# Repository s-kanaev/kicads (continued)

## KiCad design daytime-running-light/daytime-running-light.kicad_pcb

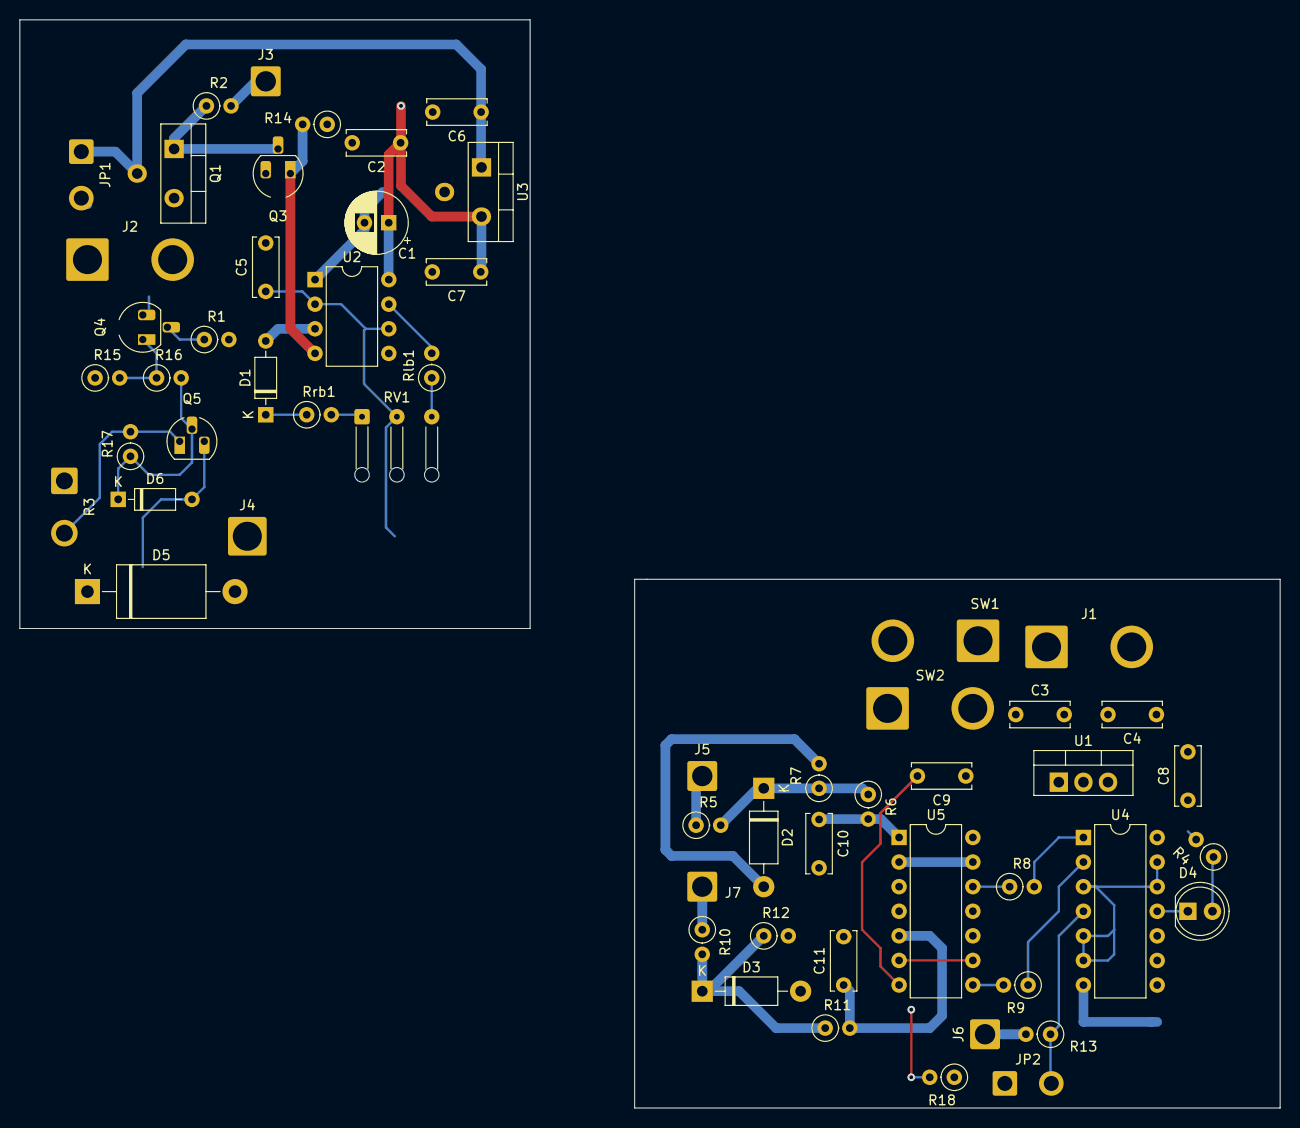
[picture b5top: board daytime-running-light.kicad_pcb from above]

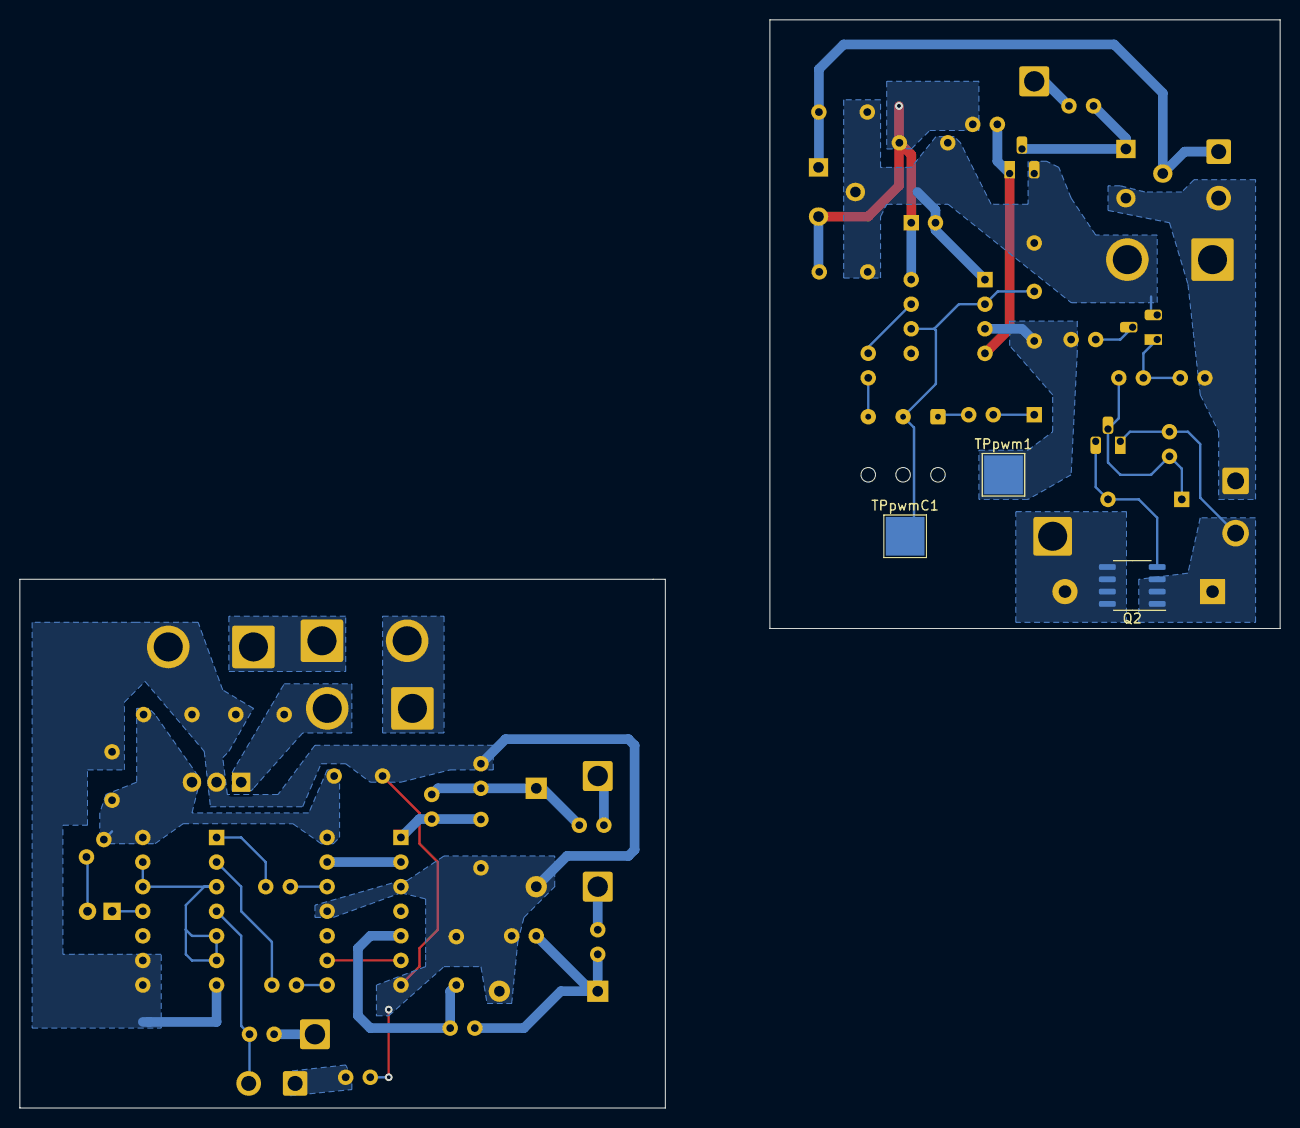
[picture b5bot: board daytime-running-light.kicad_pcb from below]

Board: 2 copper layers, 130.2 x 112.4 mm, 61 parts (3 on the bottom side), 42 nets.

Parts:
C1: 0.1u; CP_Radial_D6.3mm_P2.50mm
C2: 0.1u; C_Disc_D6.0mm_W2.5mm_P5.00mm
C3, C6, C10, C11: 0.33uF; C_Disc_D6.0mm_W2.5mm_P5.00mm
C4, C7, C8, C9: 0.1uF; C_Disc_D6.0mm_W2.5mm_P5.00mm
C5: 33n; C_Disc_D6.0mm_W2.5mm_P5.00mm
D1: BAT42; D_DO-35_SOD27_P7.62mm_Horizontal
D2: 1N47xxA; D_DO-41_SOD81_P10.16mm_Horizontal
D3: 1N4742A; D_DO-41_SOD81_P10.16mm_Horizontal
D4: LED; LED_D5.0mm
D5: 1.5KExxA; D_DO-201AE_P15.24mm_Horizontal
D6: 1N4148; D_DO-35_SOD27_P7.62mm_Horizontal
J1, J2: Conn_01x02_Socket; SolderWire-2.5sqmm_1x02_P8.8mm_D2.4mm_OD4.4mm
J3, J5, J7: Conn_01x01_Socket; SolderWire-1.5sqmm_1x01_D1.7mm_OD3mm
J4: Conn_01x01_Socket; SolderWire-2.5sqmm_1x01_D2.4mm_OD3.6mm
J6: Conn_01x01_Pin; SolderWire-1.5sqmm_1x01_D1.7mm_OD3mm
JP1, JP2: Jumper_2_Open; SolderWire-0.75sqmm_1x02_P4.8mm_D1.25mm_OD2.3mm
Q1: IRF9540N; TO-220-3_Vertical-mod
Q2: IRF9321; SO-8_3.9x4.9mm_P1.27mm
Q3, Q4: BC548; TO-92_HandSolder2
Q5: BC548; TO-92_HandSolder
R1, R2, R17: 10k; R_Axial_DIN0207_L6.3mm_D2.5mm_P2.54mm_Vertical
R3: 0.2; SolderWire-1sqmm_1x02_P5.4mm_D1.4mm_OD2.7mm
R4, R18: R; R_Axial_DIN0207_L6.3mm_D2.5mm_P2.54mm_Vertical
R5, R8, R9, R10: 1k; R_Axial_DIN0207_L6.3mm_D2.5mm_P2.54mm_Vertical
R6, R11: 47k; R_Axial_DIN0207_L6.3mm_D2.5mm_P2.54mm_Vertical
R7, R12: 100k; R_Axial_DIN0207_L6.3mm_D2.5mm_P2.54mm_Vertical
R13, R16: 100; R_Axial_DIN0207_L6.3mm_D2.5mm_P2.54mm_Vertical
R14, R15: 10k..100k; R_Axial_DIN0207_L6.3mm_D2.5mm_P2.54mm_Vertical
RV1: 51k; SolderWire-0.1sqmm_1x03_P3.6mm_D0.4mm_OD1mm_Relief
Rlb1: 51k; R_Axial_DIN0207_L6.3mm_D2.5mm_P2.54mm_Vertical
Rrb1: 1k; R_Axial_DIN0207_L6.3mm_D2.5mm_P2.54mm_Vertical
SW1, SW2: SW_SPST; SolderWire-2.5sqmm_1x02_P8.8mm_D2.4mm_OD4.4mm
TPpwm1: TestPoint; TestPoint_Pad_4.0x4.0mm
TPpwmC1: TestPoint; TestPoint_Pad_4.0x4.0mm
U1: L7812; TO-220-3_Vertical
U2: TLC555xP; DIP-8_W7.62mm
U3: L7812; TO-220-3_Vertical-mod
U4: 4001; DIP-14_W7.62mm
U5: 4069; DIP-14_W7.62mm

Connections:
+12V: J2.1, JP1.2 (B), Q1.3 (S), R3.1, R15.1
/ALLOW_POWER_ON: Q1.1 (G), Q3.2 (B), R2.1
/HEADLIGHT: J5.1, R5.1
/HIGHBEAM: J7.1, R10.1
/POWER_CONTROL: D1.2 (A), R1.2, TPpwm1.1, U2.3 (Q)
/POWER_CONTROL_INV: Q4.1 (C), R15.2, R16.1
/U1_DISCH: Rlb1.2, U2.7 (DIS)
/U1_TR: C5.1, RV1.2, TPpwmC1.1, U2.2 (TR), U2.6 (THR)
/VCC_STAB: C4.1, C8.1, C9.1, R4.2, U1.3 (OUT), U4.14 (VDD), U5.14 (VDD)
/VCC_STAB2: C1.1, C2.1, C7.1, R14.1, U2.8 (VCC), U3.3 (OUT)
GND: C3.2, C4.2, C8.2, C9.2, C10.2, C11.2, D2.2 (A), D3.2 (A), J1.2, R7.2, R12.2, R18.2, U1.2 (GND), U4.7 (VSS), U4.8, U4.9, U5.3, U5.7 (VSS), U5.11
GND2: C1.2, C2.2, C5.2, C6.2, C7.2, J2.2, Q3.3 (E), Q4.3 (E), U2.1 (GND), U3.2 (GND)
unnamed: C10.1, R6.2, U5.1
unnamed: C11.1, R11.2, U5.5
unnamed: D1.1 (K), Rrb1.1
unnamed: D2.1 (K), R5.2, R6.1, R7.1
unnamed: D3.1 (K), R10.2, R11.1, R12.1
unnamed: D4.2 (A), R4.1
unnamed: D4.1 (K), U4.11
unnamed: D5.1 (A1), Q2.3 (S), Q5.1 (C), R3.2, R17.2
unnamed: D5.2 (A2), J4.1, Q2.1 (D)
unnamed: D6.2 (A), Q2.2 (G), Q5.3 (E)
unnamed: D6.1 (K), Q5.2 (B), R16.2, R17.1
unnamed: J3.1, R2.2
unnamed: J6.1, R13.2
unnamed: C6.1, JP1.1 (A), Q1.2 (D), U3.1 (IN)
unnamed: JP2.1 (A), R18.1
unnamed: JP2.2 (B), R13.1, U4.4
unnamed: Q3.1 (C), R14.2, U2.4 (R)
unnamed: Q4.2 (B), R1.1
unnamed: R8.1, U5.12
unnamed: R8.2, U4.1
unnamed: R9.1, U4.2
unnamed: R9.2, U5.8
unnamed: RV1.1, Rrb1.2
unnamed: RV1.3, Rlb1.1
unnamed: SW1.2 (B), SW2.1 (A)
unnamed: C3.1, SW2.2 (B), U1.1 (IN)
unnamed: U4.3, U4.5, U4.6, U4.12, U4.13
unnamed: U5.6, U5.9
unnamed: U5.2, U5.13
VCC: J1.1, SW1.1 (A)

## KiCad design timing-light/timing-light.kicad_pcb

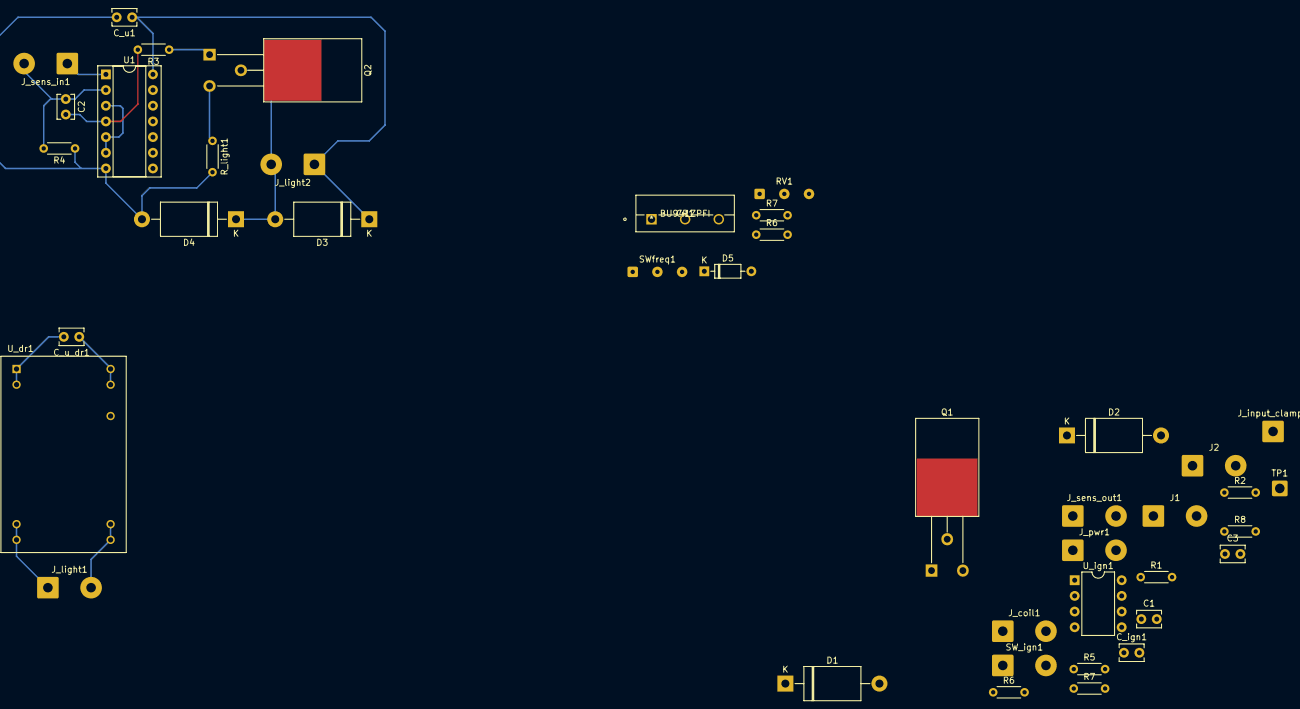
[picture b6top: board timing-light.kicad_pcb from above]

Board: 2 copper layers, 41 parts (0 on the bottom side), 28 nets.

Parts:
C1: 68pF; C_Disc_D3.8mm_W2.6mm_P2.50mm
C2: 0.1uF; C_Disc_D3.8mm_W2.6mm_P2.50mm
C3: 6.8uF; C_Disc_D3.8mm_W2.6mm_P2.50mm
CR1: BU941ZPFI
C_ign1: 0.1uF; C_Disc_D3.8mm_W2.6mm_P2.50mm
C_u1: 0.1uF; C_Disc_D3.8mm_W2.6mm_P2.50mm
C_u_dr1: 0.1uF; C_Disc_D3.8mm_W2.6mm_P2.50mm
D1, D2, D3, D4: 1.5KExxA; D_DO-201AE_P15.24mm_Horizontal
D5: BAT42; D_DO-35_SOD27_P7.62mm_Horizontal
J1: Conn_01x02_Male; SolderWire-0.75sqmm_1x02_P7mm_D1.25mm_OD3.5mm
J2: Conn_01x02_Female; SolderWire-0.75sqmm_1x02_P7mm_D1.25mm_OD3.5mm
J_coil1: Conn_01x02_Male; SolderWire-0.75sqmm_1x02_P7mm_D1.25mm_OD3.5mm
J_input_clamp1: Conn_01x01_Female; SolderWire-0.75sqmm_1x01_D1.25mm_OD3.5mm
J_light1, J_light2: Conn_01x02_Male; SolderWire-0.75sqmm_1x02_P7mm_D1.25mm_OD3.5mm
J_pwr1: Conn_01x02_Female; SolderWire-0.75sqmm_1x02_P7mm_D1.25mm_OD3.5mm
J_sens_in1: Conn_01x02_Female; SolderWire-0.75sqmm_1x02_P7mm_D1.25mm_OD3.5mm
J_sens_out1: Conn_01x02_Male; SolderWire-0.75sqmm_1x02_P7mm_D1.25mm_OD3.5mm
Q1, Q2: IRFB3004PbF; TO-220-3-4_Horizontal_TabDown
R1, R6, R7: 15k; R_Axial_DIN0204_L3.6mm_D1.6mm_P5.08mm_Horizontal
R2: 3k; R_Axial_DIN0204_L3.6mm_D1.6mm_P5.08mm_Horizontal
R3: 1k/4.7k; R_Axial_DIN0204_L3.6mm_D1.6mm_P5.08mm_Horizontal
R4: 100k; R_Axial_DIN0204_L3.6mm_D1.6mm_P5.08mm_Horizontal
R5: R; R_Axial_DIN0204_L3.6mm_D1.6mm_P5.08mm_Horizontal
R6#2, R7#2: 1k; R_Axial_DIN0204_L3.6mm_D1.6mm_P5.08mm_Horizontal
R8: 68k; R_Axial_DIN0204_L3.6mm_D1.6mm_P5.08mm_Horizontal
RV1: 470k; SolderWire-0.15sqmm_1x03_P4mm_D0.5mm_OD1.5mm
R_light1: R; R_Axial_DIN0204_L3.6mm_D1.6mm_P5.08mm_Horizontal
SW_ign1: SW_SPST; SolderWire-0.75sqmm_1x02_P7mm_D1.25mm_OD3.5mm
SWfreq1: SW_SPDT; SolderWire-0.15sqmm_1x03_P4mm_D0.5mm_OD1.5mm
TP1: TestPoint; SolderWire-0.75sqmm_1x01_D1.25mm_OD2.3mm
U1: 4001; DIP-14_W7.62mm_Socket
U_dr1: LDB600; MEANWELL_LDB-350L
U_ign1: TLC555xP; DIP-8_W7.62mm

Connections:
+12V: C_u1.1, C_u_dr1.1, D1.1 (A1), D3.1 (A1), J_coil1.1, J_light2.1, J_pwr1.2, SW_ign1.1 (A), U1.14 (VDD), U_dr1.23 (+Vin), U_dr1.24 (+Vin)
/U_ign_pwr: C_ign1.1, SW_ign1.2 (B), U_ign1.4 (R), U_ign1.8 (VCC)
/U_ign_tr: C3.1, R7.2, R8.2
/Uign_dis: R7#2.2, U_ign1.7 (DIS)
/Uign_trig: RV1.2, SWfreq1.2 (B), U_ign1.2 (TR), U_ign1.6 (THR)
/on_off_dr: Q2.1 (G), R3.1, U_dr1.21 (PWM_DIM)
GND: C3.2, CR1.3 (E), C_ign1.2, C_u1.2, C_u_dr1.2, D2.2 (A2), D4.2 (A2), J1.1, J2.1, J_pwr1.1, Q1.3, R4.1, R_light1.2, U1.7 (VSS), U_dr1.1 (-Vin), U_dr1.2 (-Vin), U_ign1.1 (GND)
unnamed: C1.1, R1.2, R2.2
unnamed: C1.2, J_input_clamp1.1
unnamed: C2.1, J_sens_in1.2, R4.2, U1.2
unnamed: C2.2, R3.2, U1.4
unnamed: CR1.1 (B), J2.2
unnamed: CR1.2 (C), D1.2 (A2), D2.1 (A1), J_coil1.2
unnamed: Q1.2, Q1.4
unnamed: D3.2 (A2), D4.1 (A1), J_light2.2, Q2.2 (D), Q2.4 (D)
unnamed: D5.1 (K), R6#2.1
unnamed: D5.2 (A), R5.2, TP1.1, U_ign1.3 (Q)
unnamed: J1.2, R5.1
unnamed: J_light1.1, U_dr1.11 (-Vout), U_dr1.12 (-Vout)
unnamed: J_light1.2, U_dr1.13 (+Vout), U_dr1.14 (+Vout)
unnamed: J_sens_in1.1, U1.1
unnamed: J_sens_out1.1, R1.1
unnamed: J_sens_out1.2, R2.1
unnamed: Q2.3 (S), R_light1.1
unnamed: R6.1, R7.1
unnamed: R6.2, R6#2.2, R8.1, RV1.3
unnamed: R7#2.1, RV1.1
unnamed: U1.3, U1.5, U1.6

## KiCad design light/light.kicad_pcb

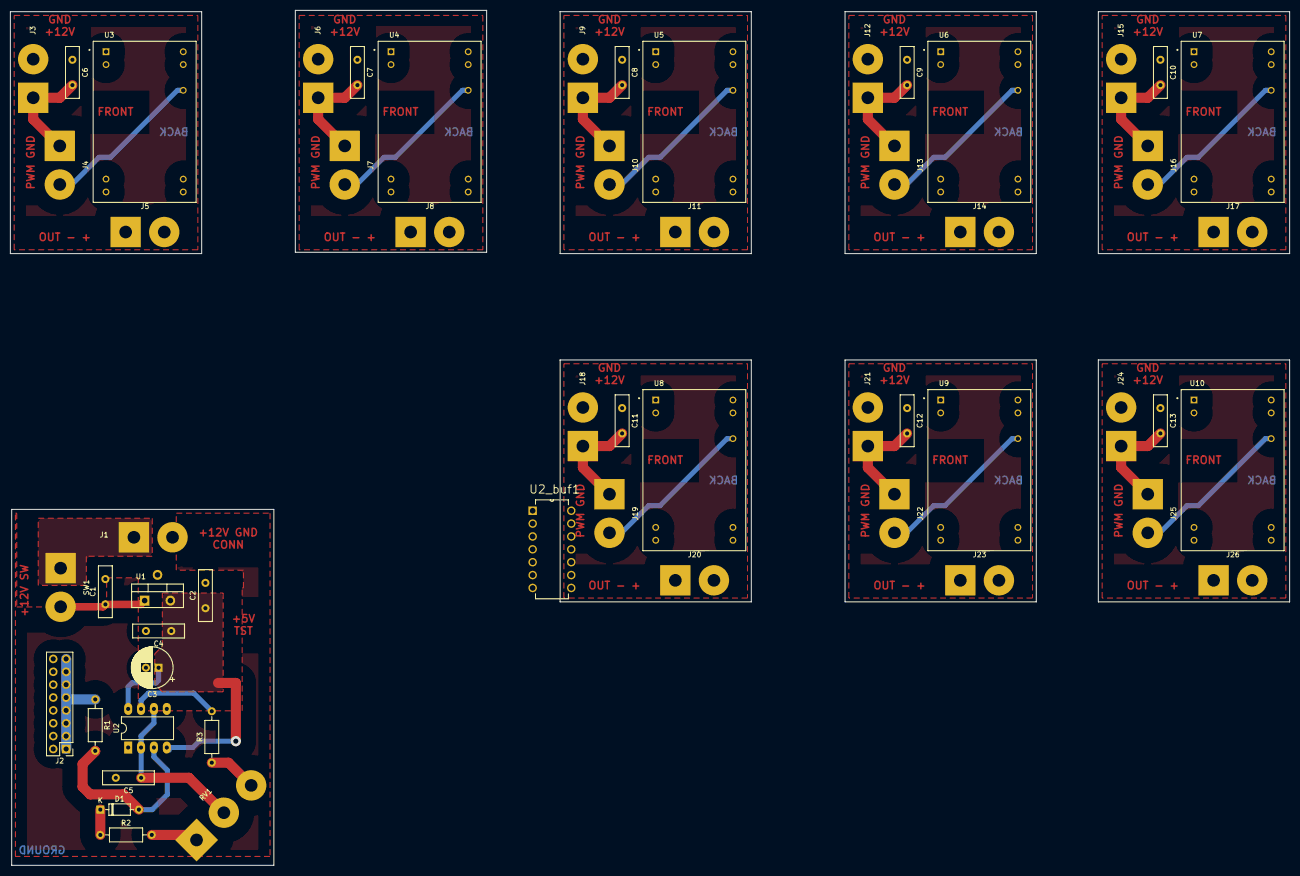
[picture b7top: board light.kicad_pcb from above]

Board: 2 copper layers, 252.5 x 168.8 mm, 56 parts (0 on the bottom side), 55 nets.

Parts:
C1: 0.33u; C_Disc_D10.0mm_W2.5mm_P5.00mm
C2, C4: 0.1u; C_Disc_D10.0mm_W2.5mm_P5.00mm
C3: 1u; CP_Radial_D8.0mm_P2.50mm
C5: 33n; C_Disc_D10.0mm_W2.5mm_P5.00mm
C6, C7, C8, C9, C10, C11, C12, C13: 1u; C_Disc_D10.0mm_W2.5mm_P5.00mm
D1: BAT42; D_DO-35_SOD27_P7.62mm_Horizontal
J1, J3, J4, J6, J7, J9, J10, J12, J13, J15, J16, J18, J19, J21, J22, J24, J25: Conn_01x02_Female; SolderWirePad_1x02_P7.62mm_Drill2.5mm
J2: Conn_02x08_Odd_Even; PinHeader_2x08_P2.54mm_Vertical
J5, J8, J11, J14, J17, J20, J23, J26: Conn_01x02_Male; SolderWirePad_1x02_P7.62mm_Drill2.5mm
R1: 100; R_Axial_DIN0207_L6.3mm_D2.5mm_P10.16mm_Horizontal
R2, R3: 1k; R_Axial_DIN0207_L6.3mm_D2.5mm_P10.16mm_Horizontal
RV1: 100k; SolderWirePad_1x03_P7.62mm_Drill2.5mm
SW1: SW_SPST; SolderWirePad_1x02_P7.62mm_Drill2.5mm
U1: L7805; TO-220-3_Vertical-mod2
U2: TLC555CPS; DIP-8_W7.62mm_LongPads
U2_buf1: 74HC125N; DIP254P762X420-14
U3, U4, U5, U6, U7, U8, U9, U10: LDB600; MEANWELL_LDB-350L

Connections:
+5V: C2.1, C3.1, C4.1, U1.3 (OUT), U2.4 (R), U2.8 (VCC), U2_buf1.14 (VCC)
+12V: J1.1, SW1.1 (A)
/PWM_disch: R3.2, U2.7 (DIS)
/PWM_tr: C5.1, RV1.2, U2.2 (TR), U2.6 (THR)
/pwm_out: R1.1, U2_buf1.2 (1A), U2_buf1.5 (2A), U2_buf1.9 (3A), U2_buf1.12 (4A)
GND: C1.2, C2.2, C3.2, C4.2, C5.2, J1.2, J2.2, J2.4, J2.6, J2.8, J2.10, J2.12, J2.14, J2.16, U1.2 (GND), U2.1 (GND), U2_buf1.1 (1~OE), U2_buf1.4 (2~OE), U2_buf1.7 (GND), U2_buf1.10 (3~OE), U2_buf1.13 (4~OE)
unnamed: C1.1, SW1.2 (B), U1.1 (IN)
unnamed: C6.1, J3.2, U3.23 (+Vin), U3.24 (+Vin)
unnamed: C6.2, J3.1, J4.1, U3.1 (-Vin), U3.2 (-Vin)
unnamed: C7.1, J6.2, U4.23 (+Vin), U4.24 (+Vin)
unnamed: C7.2, J6.1, J7.1, U4.1 (-Vin), U4.2 (-Vin)
unnamed: C8.1, J9.2, U5.23 (+Vin), U5.24 (+Vin)
unnamed: C8.2, J9.1, J10.1, U5.1 (-Vin), U5.2 (-Vin)
unnamed: C9.1, J12.2, U6.23 (+Vin), U6.24 (+Vin)
unnamed: C9.2, J12.1, J13.1, U6.1 (-Vin), U6.2 (-Vin)
unnamed: C10.1, J15.2, U7.23 (+Vin), U7.24 (+Vin)
unnamed: C10.2, J15.1, J16.1, U7.1 (-Vin), U7.2 (-Vin)
unnamed: C11.1, J18.2, U8.23 (+Vin), U8.24 (+Vin)
unnamed: C11.2, J18.1, J19.1, U8.1 (-Vin), U8.2 (-Vin)
unnamed: C12.1, J21.2, U9.23 (+Vin), U9.24 (+Vin)
unnamed: C12.2, J21.1, J22.1, U9.1 (-Vin), U9.2 (-Vin)
unnamed: C13.1, J24.2, U10.23 (+Vin), U10.24 (+Vin)
unnamed: C13.2, J24.1, J25.1, U10.1 (-Vin), U10.2 (-Vin)
unnamed: D1.1 (K), R2.1
unnamed: D1.2 (A), R1.2, U2.3 (Q)
unnamed: J2.1, J2.3, U2_buf1.3 (1Y)
unnamed: J2.5, J2.7, U2_buf1.6 (2Y)
unnamed: J2.9, J2.11, U2_buf1.8 (3Y)
unnamed: J2.13, J2.15, U2_buf1.11 (4Y)
unnamed: J4.2, U3.21 (PWM_DIM)
unnamed: J5.1, U3.11 (-Vout), U3.12 (-Vout)
unnamed: J5.2, U3.13 (+Vout), U3.14 (+Vout)
unnamed: J7.2, U4.21 (PWM_DIM)
unnamed: J8.1, U4.11 (-Vout), U4.12 (-Vout)
unnamed: J8.2, U4.13 (+Vout), U4.14 (+Vout)
unnamed: J10.2, U5.21 (PWM_DIM)
unnamed: J11.1, U5.11 (-Vout), U5.12 (-Vout)
unnamed: J11.2, U5.13 (+Vout), U5.14 (+Vout)
unnamed: J13.2, U6.21 (PWM_DIM)
unnamed: J14.1, U6.11 (-Vout), U6.12 (-Vout)
unnamed: J14.2, U6.13 (+Vout), U6.14 (+Vout)
unnamed: J16.2, U7.21 (PWM_DIM)
unnamed: J17.1, U7.11 (-Vout), U7.12 (-Vout)
unnamed: J17.2, U7.13 (+Vout), U7.14 (+Vout)
unnamed: J19.2, U8.21 (PWM_DIM)
unnamed: J20.1, U8.11 (-Vout), U8.12 (-Vout)
unnamed: J20.2, U8.13 (+Vout), U8.14 (+Vout)
unnamed: J22.2, U9.21 (PWM_DIM)
unnamed: J23.1, U9.11 (-Vout), U9.12 (-Vout)
unnamed: J23.2, U9.13 (+Vout), U9.14 (+Vout)
unnamed: J25.2, U10.21 (PWM_DIM)
unnamed: J26.1, U10.11 (-Vout), U10.12 (-Vout)
unnamed: J26.2, U10.13 (+Vout), U10.14 (+Vout)
unnamed: R2.2, RV1.3
unnamed: R3.1, RV1.1

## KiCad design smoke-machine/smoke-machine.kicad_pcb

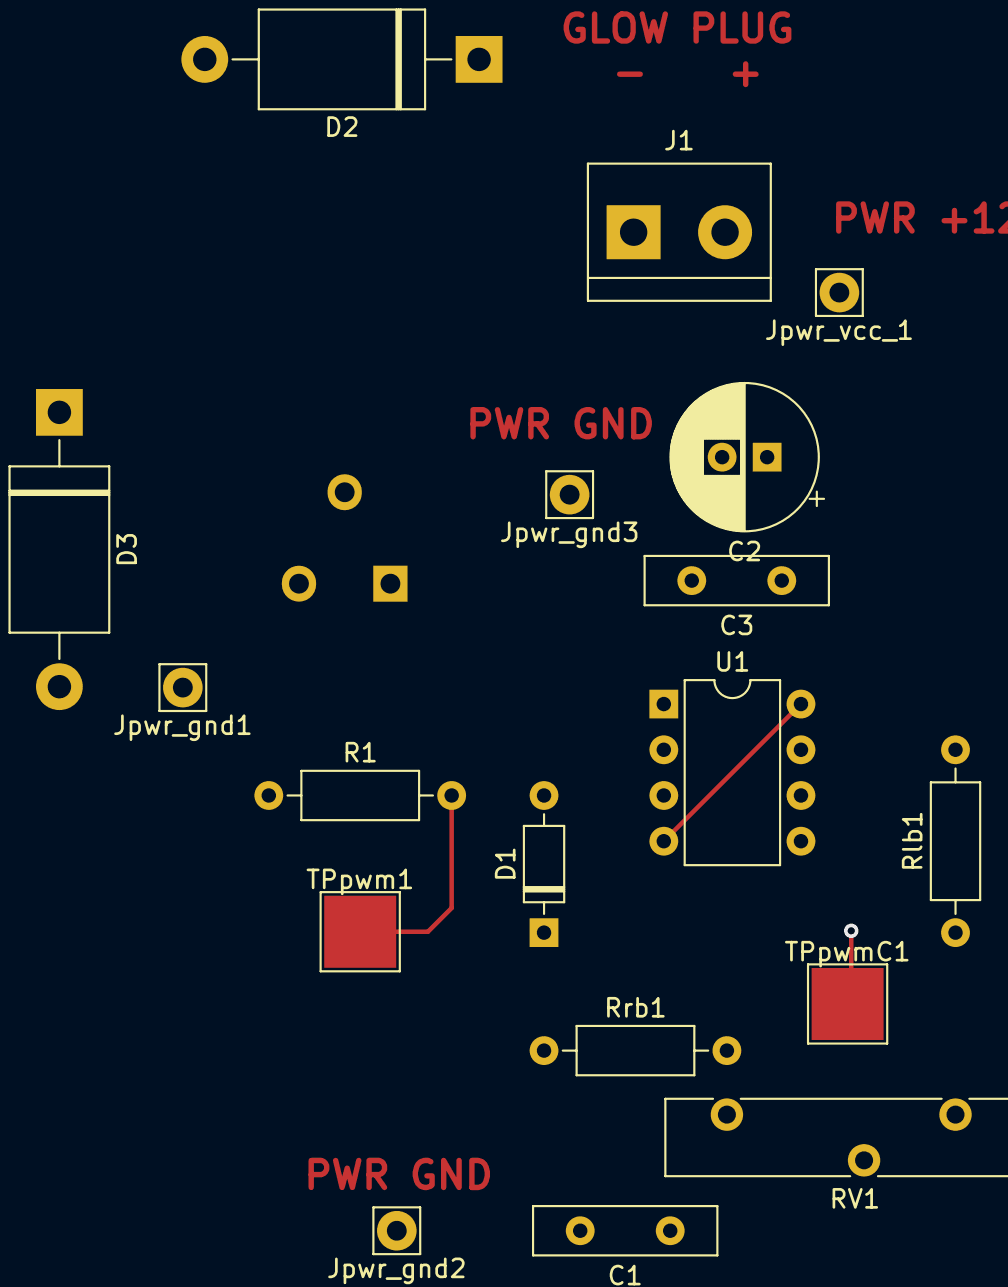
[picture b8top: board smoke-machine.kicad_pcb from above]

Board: 2 copper layers, 19 parts (1 on the bottom side), 12 nets.

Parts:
C1: 33n; C_Disc_D10.0mm_W2.5mm_P5.00mm
C2: 1u; CP_Radial_D8.0mm_P2.50mm
C3: 0.1u; C_Disc_D10.0mm_W2.5mm_P5.00mm
D1: BAT42; D_DO-35_SOD27_P7.62mm_Horizontal
D2, D3: 1.5KExxA; D_DO-201AE_P15.24mm_Horizontal
J1: Conn_01x02_Female; TerminalBlock_bornier-2_P5.08mm
Jpwr_gnd1, Jpwr_gnd2, Jpwr_gnd3: Conn_01x01_Female; Pin_D1.1mm_L8.5mm_W2.5mm_FlatFork
Jpwr_vcc_1: Conn_01x01_Female; Pin_D1.1mm_L8.5mm_W2.5mm_FlatFork
Q1: IRFB3004PbF; TO-220-3-4_Horizontal_TabDown
R1: 100..1k; R_Axial_DIN0207_L6.3mm_D2.5mm_P10.16mm_Horizontal
RV1: 100k; Potentiometer_Bourns_3005_Horizontal
Rlb1: 1k; R_Axial_DIN0207_L6.3mm_D2.5mm_P10.16mm_Horizontal
Rrb1: 1k; R_Axial_DIN0207_L6.3mm_D2.5mm_P10.16mm_Horizontal
TPpwm1: TestPoint; TestPoint_Pad_4.0x4.0mm
TPpwmC1: TestPoint; TestPoint_Pad_4.0x4.0mm
U1: NE555; DIP-8_W7.62mm

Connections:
/PWM_OUT: Q1.1, R1.1
/PWR_GND_1: D3.2, Jpwr_gnd1.1, Q1.3
/PWR_GND_2: C1.2, Jpwr_gnd2.1
/PWR_GND_3: C2.2, C3.2, Jpwr_gnd3.1, U1.1
/PWR_VCC_1: C2.1, C3.1, D2.1, J1.2, Jpwr_vcc_1.1, U1.4, U1.8
/U1_DISCH: Rlb1.2, U1.7
/U1_TR: C1.1, RV1.2, TPpwmC1.1, U1.2, U1.6
unnamed: D1.1, Rrb1.1
unnamed: D1.2, R1.2, TPpwm1.1, U1.3
unnamed: D2.2, D3.1, J1.1, Q1.2, Q1.4
unnamed: RV1.1, Rrb1.2
unnamed: RV1.3, Rlb1.1

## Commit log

2021-02-26 Init light prj
2021-03-06 [ligh] Finish
2021-03-06 [find-wire] Finish
2022-06-01 [light] Finish
2022-06-01 [smoke-machine] backup
2022-06-01 [spot-welding] backup
2022-06-01 [timing-light] backup
2022-06-08 [LIB] backup
2022-08-10 Remove unwanted files
2022-08-10 [light] update
2022-08-10 [spot-welding] update
2022-08-10 [timing-light] update
2022-08-10 [T sensor model] Start temperature sensor model/stub
2022-09-05 [timing-light] Use BU941ZP as ignition coil driver
2022-12-27 [T sensor model] Update temp sensor model
2022-12-27 [timing-light] Use add BU941ZP for update later
2023-02-16 [LIB] Add TPS2814D
2023-03-14 [diag] Add cooler working diagnostic schematic
2023-05-12 Update smoke-machine project
2023-05-12 Add .gitignore
2023-05-12 [soft-start] Add fan motor soft-start
2023-05-13 [soft-start] Add power supply
2023-05-20 [soft-start] Add PCB
2023-05-21 [soft-start] Small changes
2023-08-17 [LIB] Update lib
2023-08-17 [drl] Add daytime running light schem and start pcb
2023-08-26 [drl] Change daytime running light to use TLC555 timer.
2023-08-28 [drl] Update
2023-10-13 [LIB] Add modified hand soldered TO-92 package
2023-10-13 [drl] Change schematic and PCB
2023-10-17 [LIB] add BYV32E-200
2023-10-30 [soft-start] Update to use counter as time delay source
2023-11-01 [soft-start] Update schematic and add PCB
2023-11-06 [soft-start] Update PCB - decrease dimensions, remove hard tracks.
2023-11-06 [soft-start] Schematic - set values for C4 and C5
2023-11-18 [soft-start] Schematic - add fixes for trigger. Update PCB.
2023-11-18 [soft-start] Add PWM soft-start schematic and PCB. Should be updated with distinct parts' values and fixes.
2023-11-27 [LIB] Expand library with VCC2, +BATT2, thyristor symbols, IRS10752L
2023-11-27 [soft-start] Update values of timing RC
2023-11-27 [soft-start] Add calculus file. Add integrating and comparator schematic for turning on full-power.
2023-11-27 [LIB] Add P0102BL thyristor value field
2023-11-27 [soft-start] Change comparator. Start PCB.
2023-11-29 [DRL] Add DRL with N-channel MOSFET
2023-11-29 [soft-start] Complete basic PCB for PWM soft-start
2023-11-30 [DRL] [soft-start] Update track widths. Prepare for plotting
2023-11-30 Add output to .gitignore
2023-12-02 [drl] Update plot settings
2023-12-02 [soft-start] Reset PWM generator on trigger latch. Update plot settings
2023-12-04 [soft-start] Add capacitor discharge resistor. It limits capacitor voltage to approx. 90% of VCC
2023-12-05 [DRL] Fix and update PCB and schematic Use BAT2 and VCC2 Add missing net on PCB Improve zones for BAT2 and GND2
2023-12-08 [LIB] Update legecy symbol libraries. Add AUIRF2804S symbol and modified footprint
2023-12-08 [adapter] Add adapters from SOIC-8 etc. to DIP for bread boards
2023-12-08 [DRL] Improve schematic and PCB
2023-12-15 [adapter] Update PCB
2023-12-16 [drl] Add proteus modeling schematic
2023-12-16 [drl] Update proteus modeling project
2023-12-17 [drl] Add proper voltage bootstrap powered from a double voltage. Start reimpl PCB
2023-12-17 [drl] Finish PCB.
    TODO - fix DRC.
2023-12-18 [drl] Fix design rules check
2023-12-20 [drl] Update some zones and traces on PCB. Fix DRC. Reduce size of ctrl PCB. Add zones for headlight and highbeam connection.
2023-12-29 [drl] Add distinct generator for voltage doubler in modeiling schematic. TODO: test and move to kicad schema and PCB
2024-01-05 [drl] Test this circuit
